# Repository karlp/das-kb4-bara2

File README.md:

## Das Keyboard 4 controller replacement - usb2 only.

I had a mains accident with my [das keyboard](https://www.daskeyboard.com/daskeyboard-4-professional/), and blew out the USB3 hub, the Via xxxxfixmexx part.  
I sourced a replacement, but it never came up, so perhaps it was more broken.

Today, I've had the idea of just making a replacement controller board for it.  They _keys_ are presumably all still fine.

So... Pick a cheap in stock MCU supported by [QMK](https://qmk.fm/), just go for a plain USB2-HS hub part, and.. profit?

## Status
[Have a working version](h2/r2023-12), though the layout was somewhat poorly thought out. It's not as cheap in assembly and manufacturing as the rest of the design might imply.

## TODO
 * Make a cheaper version, with better mechanical fit.
 * apply for a OSHW number?)

## License
Consider this "open hardware"

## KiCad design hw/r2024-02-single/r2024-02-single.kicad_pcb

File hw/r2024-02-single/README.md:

## What's it like?

## Status

initial stages only

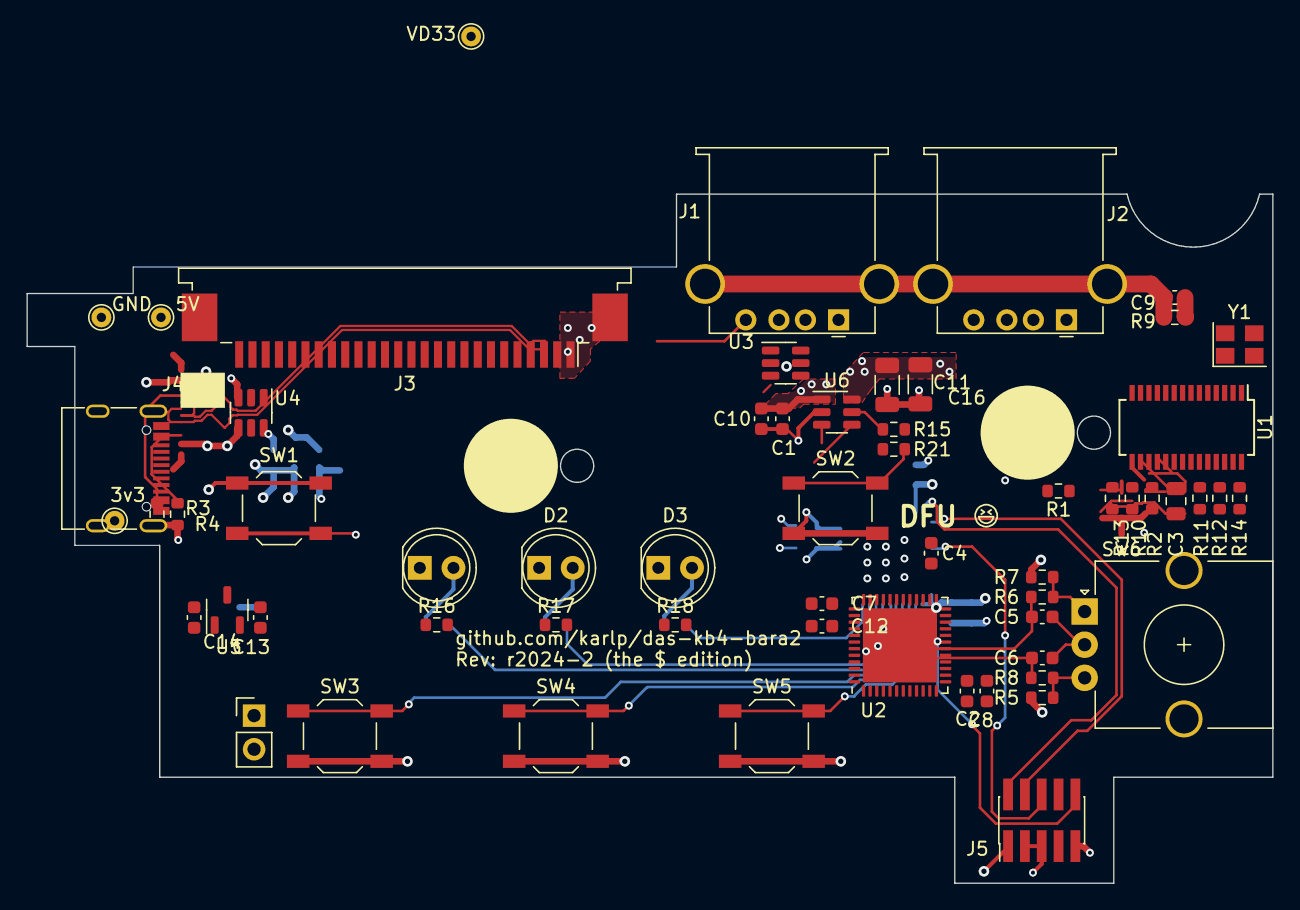
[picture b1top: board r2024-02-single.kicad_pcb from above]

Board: 4 copper layers, 94.0 x 52.0 mm, 60 parts (0 on the bottom side), 69 nets.

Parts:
C1, C2, C4, C7, C9: 100nF; C_0603_1608Metric
C3: 10uF; C_0805_2012Metric
C5, C6: 10nF; C_0603_1608Metric
C8, C10, C12, C13, C14: 1uF; C_0603_1608Metric
C11, C16: 100uF; C_1206_3216Metric
D1: NUM_LOCK; LED_D5.0mm
D2: CAPS_LOCK; LED_D5.0mm
D3: SCROLL_LOCK; LED_D5.0mm
J1, J2: USB_A; USB_A_Stewart_SS-52100-001_Horizontal
J3: Conn_01x26_Socket; TE_2-84952-6_1x26-1MP_P1.0mm_Horizontal
J4: USB_C_Receptacle_USB2.0; USB_C_Receptacle_G-Switch_GT-USB-7010ASV
J5: Conn_ARM_JTAG_SWD_10; PinHeader_2x05_P1.27mm_Vertical_SMD
JP3: Jumper_2_Open; PinHeader_1x02_P2.54mm_Vertical
R1: 2k7/1%; R_0603_1608Metric
R2, R5, R6, R7, R8, R11, R12, R13, R14, R15, R21: 10k; R_0603_1608Metric
R3, R4: 5k1; R_0603_1608Metric
R9, R16, R17, R18: 220; R_0603_1608Metric
R10: 0; R_0603_1608Metric
SW1: PWR; SW_SPST_TL3342
SW2: MUTE; SW_SPST_TL3342
SW3: PREV; SW_SPST_TL3342
SW4: PLAY_PAUSE; SW_SPST_TL3342
SW5: NEXT; SW_SPST_TL3342
SW6: Volume; RotaryEncoder_Alps_EC12E_Vertical_H20mm_CircularMountingHol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
TP1: 5V; TestPoint_THTPad_D1.5mm_Drill0.7mm
TP2: 3v3; TestPoint_THTPad_D1.5mm_Drill0.7mm
TP3: GND; TestPoint_THTPad_D1.5mm_Drill0.7mm
TP4: VD33; TestPoint_THTPad_D1.5mm_Drill0.7mm
U1: FE1.1s; SSOP-28_3.9x9.9mm_P0.635mm
U2: STM32G431CBUx; QFN-48-1EP_7x7mm_P0.5mm_EP5.6x5.6mm
U3, U4: SRV05-4; SOT-23-6
U5: XC6206PxxxMR; SOT-23-3
U6: AP2552W6; SOT-23-6
Y1: 12MHz; Crystal_SMD_3225-4Pin_3.2x2.5mm

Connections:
+3V3: C2.2, C4.2, C7.2, C8.1, C12.1, C14.1, J5.1 (VTref), R5.1, R7.1, SW1.2, SW2.2, SW3.2, SW4.2, SW5.2, TP2.1, U2.1 (VBAT), U2.20 (VREF+), U2.21 (VDDA), U2.23 (VDD), U2.35 (VDD), U2.48 (VDD), U5.2 (VO)
+5V: C1.2, C10.1, C13.1, J4.A4 (VBUS), J4.A9 (VBUS), J4.B4 (VBUS), J4.B9 (VBUS), R10.1, R12.1, R13.1, R14.1, TP1.1, U1.18 (VBUSM), U1.20 (VDD5), U4.5 (VBUS), U5.3 (VI), U6.1 (IN)
/keys_mcu/CAPS_LOCK: R17.1, U2.6 (PF1)
/keys_mcu/CM1: J3.21, U2.40 (PC11)
/keys_mcu/CM2: J3.6, U2.17 (PB0)
/keys_mcu/CM3: J3.7, U2.18 (PB1)
/keys_mcu/CM4: J3.8, U2.19 (PB2)
/keys_mcu/CM5: J3.22, U2.42 (PB4)
/keys_mcu/CM6: J3.23, U2.43 (PB5)
/keys_mcu/CM7: J3.24, U2.44 (PB6)
/keys_mcu/CM9: J3.26, U2.47 (PB9)
/keys_mcu/CM10: J3.15, U2.29 (PC6)
/keys_mcu/CM11: J3.9, U2.22 (PB10)
/keys_mcu/CM12: J3.10, U2.24 (PB11)
/keys_mcu/CM13: J3.11, U2.25 (PB12)
/keys_mcu/CM14: J3.12, U2.26 (PB13)
/keys_mcu/CM15: J3.13, U2.27 (PB14)
/keys_mcu/CM16: J3.14, U2.28 (PB15)
/keys_mcu/CM17: J3.20, U2.39 (PC10)
/keys_mcu/CM18: J3.19, U2.38 (PA15)
/keys_mcu/CM19: J3.1, U2.12 (PA4)
/keys_mcu/CM20: J3.2, U2.13 (PA5)
/keys_mcu/CM21: J3.3, U2.14 (PA6)
/keys_mcu/CM22: J3.4, U2.15 (PA7)
/keys_mcu/CM23: J3.16, U2.30 (PA8)
/keys_mcu/CM24: J3.17, U2.31 (PA9)
/keys_mcu/CM25: J3.18, U2.32 (PA10)
/keys_mcu/CM26: J3.5, U2.16 (PC4)
/keys_mcu/ENC_A: C5.1, R6.1, U2.8 (PA0)
/keys_mcu/ENC_B: C6.1, R8.2, U2.9 (PA1)
/keys_mcu/NRST: J5.10 (~RESET), U2.7 (PG10)
/keys_mcu/NUM_LOCK: R16.1, U2.5 (PF0)
/keys_mcu/SCROLL_LOCK: R18.1, U2.10 (PA2)
/keys_mcu/SW1: SW1.1, U2.11 (PA3)
/keys_mcu/SW2: R21.2, SW2.1, U2.46 (PB8)
/keys_mcu/SW3: SW3.1, U2.4 (PC15)
/keys_mcu/SW4: SW4.1, U2.3 (PC14)
/keys_mcu/SW5: SW5.1, U2.2 (PC13)
/keys_mcu/SWD_CLK: J5.4 (SWCLK/TCK), U2.37 (PA14)
/keys_mcu/SWD_IO: J5.2 (SWDIO/TMS), U2.36 (PA13)
/keys_mcu/SWO: J5.6 (SWO/TDO), U2.41 (PB3)
/usb/BUSJ: R2.1, R10.2, U1.19 (BUSJ)
/usb/ILIM: R15.1, U6.5 (ILIM)
/usb/PWR_EN: U1.25 (PWRJ), U6.3 (~EN)
/usb/PWR_OC: R14.2, U1.26 (OVCJ), U6.4 (~FLG)
/usb/UDS1N: J1.2 (D-), U1.10 (DM1), U3.6 (I/O4)
/usb/UDS1P: J1.3 (D+), U1.11 (DP1), U3.1 (I/O1)
/usb/UDS2N: J2.2 (D-), U1.8 (DM2), U3.4 (I/O3)
/usb/UDS2P: J2.3 (D+), U1.9 (DP2), U3.3 (I/O2)
/usb/UUPN: J4.A7 (D-), J4.B7 (D-), U1.15 (DMU), U4.3 (I/O2)
/usb/UUPP: J4.A6 (D+), J4.B6 (D+), U1.16 (DPU), U4.4 (I/O3)
/usb/VD33: C3.1, TP4.1, U1.13 (VD33), U1.21 (VD33_O)
GND: C1.1, C2.1, C3.2, C4.1, C5.2, C6.2, C7.1, C8.2, C9.1, C10.2, C11.2, C12.2, C13.2, C14.2, C16.2, D1.1 (K), D2.1 (K), D3.1 (K), J1.4 (GND), J2.4 (GND), J4.A1 (GND), J4.A12 (GND), J4.B1 (GND), J4.B12 (GND), J4.S1 (SHIELD), J5.3 (GND), J5.5 (GND), J5.9 (GNDDetect), JP3.1 (A), JP3.2 (B), R1.2, R2.2, R3.2, R4.2, R9.1, R11.1, R15.2, R21.1, SW6.C, TP3.1, U1.1 (VSS), U2.49 (VSS), U3.2 (GND), U4.2 (GND), U5.1 (GND), U6.2 (GND), Y1.2, Y1.4
GNDPWR: C9.2, J1.5 (Shield), J2.5 (Shield), R9.2
unnamed: D1.2 (A), R16.2
unnamed: D2.2 (A), R17.2
unnamed: D3.2 (A), R18.2
unnamed: J4.A5 (CC1), R3.1
unnamed: J4.B5 (CC2), R4.1
unnamed: R5.2, R8.1, SW6.B
unnamed: R6.2, R7.2, SW6.A
unnamed: R11.2, R12.2, U1.22 (DRV)
unnamed: R1.1, U1.14 (REXT)
unnamed: U1.3 (XIN), Y1.3
unnamed: U1.2 (XOUT), Y1.1
unnamed: R13.2, U1.17 (~XRSTJ)
UMCU_N: U1.6 (DM3), U2.33 (PA11)
UMCU_P: U1.7 (DP3), U2.34 (PA12)
VBUS: C11.1, C16.1, J1.1 (VBUS), J2.1 (VBUS), U3.5 (VBUS), U6.6 (OUT)

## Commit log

2023-11-13 initial joy
2023-11-15 sch nearing completion.
    usb side done.
    needs mcu power supply sorting out.
2023-11-15 make note that this will be / is open hardware
2023-11-16 schematic "done" footprints all assigned
    Need working calipers to start getting the board outline and fixed
    positions, but ... mostly there?
    schematic needs "polish" now, more introductions, cleaner text layouts,
    probably more optional test points, throw more caps at it.
2023-11-16 initial freecad board outline.
    We didn't include all the switches/leds, and in the end, we allowed
    ourselves more room for the usb-c connector. The original board uses a
    _very_ shallow micro-b3 connector, which leaves no room for the
    power/suspend switch, and there's enough space in the chassis to expand
    in that direction a few mm.
2023-11-16 import board outline and lock fixed items
    No routing, just rough placement of all the fixed items.
2023-11-26 update readme with real links
2023-11-26 add "bonus" can transceiver ;)
    this is so we can use the round 1 protos for another project...
    also: replace srv05 with an alternate, also jlc preferred, but cheaper
    part. Update power budgets.
    We've done some initial work with the pcb, but we're running into weird
    kicad wx bugs, so we're going to save it all here, and commit, and
    perhaps continue with 7.99.....
2023-11-26 Add can txer datasheet
2023-11-26 gitignore more backup files
2023-11-29 routing progress
    Just nice to make some save points every now and again.
    USB seems... ok? Still need to check 3v3 or 5v on the power pullups,
2023-11-30 cleanup schematic, break out most of it
    Broke it all out to the right places, now I can go and shuffle all the
    labels to make it line up. Thankfully we can just "freely" route the
    keybaord matrix pins!
2023-12-01 unrouted: 0
    Juggled all the key matrix IOs and reviewed "all" outstanding TODOs
    left: add another cap for downstream Vbus. it's free, and can only
    help.
    left: lots of silk?
    left: place as much free io to pads as can be easily done, for
    test/board reuse.
2023-12-04 shuffled, added bonus, silked up...
    Nearly there..?
2023-12-04 fix some erc/drc
2023-12-04 review model for usb a
2023-12-04 move to a lower directory tree
2023-12-05 some pointless irrelevant change after generating gerbers that I can't see
    kicad occasionally does that...
2023-12-12 r2023-12: one last silk update
    We're just going to pay to get a rev done. merry christmas me or
    something. no more faffing about, just get a revision back and stop
    wasting time.
2023-12-12 r2023-12: add more gnd pins
2023-12-12 r2023-12: Add production files
    Rotations are still bogus, but whatever. manually cleaned up
2023-12-12 readme for r2023-12
2023-12-12 add revision and pdf for posterity
    kicanvas is good, but let's not rely on it
2023-12-27 got first r2023-12 back.
    works, dfu shows up. no obvious fuckups then. but see the readme, the
    frame doesn't fit properly.
2023-12-27 r2023-12: add row/column notes
    We got valuable notes from: https://github.com/qmk/qmk_firmware/blob/master/keyboards/handwired/daskeyboard/daskeyboard4/info.json
    We don't have a fully working keyboard yet, but it's nearly there.
2024-01-29 r2023_12: add firmware notes and comments on matrix decode
    No intentional changes, just text added while working out the firmware.
2024-01-29 r2024-2: initial steps
    Preliminary corrections for physical layout. Added holes, keepouts, and
    moved everything to the right side.
    It's kinda starting all over again isn't it :)
